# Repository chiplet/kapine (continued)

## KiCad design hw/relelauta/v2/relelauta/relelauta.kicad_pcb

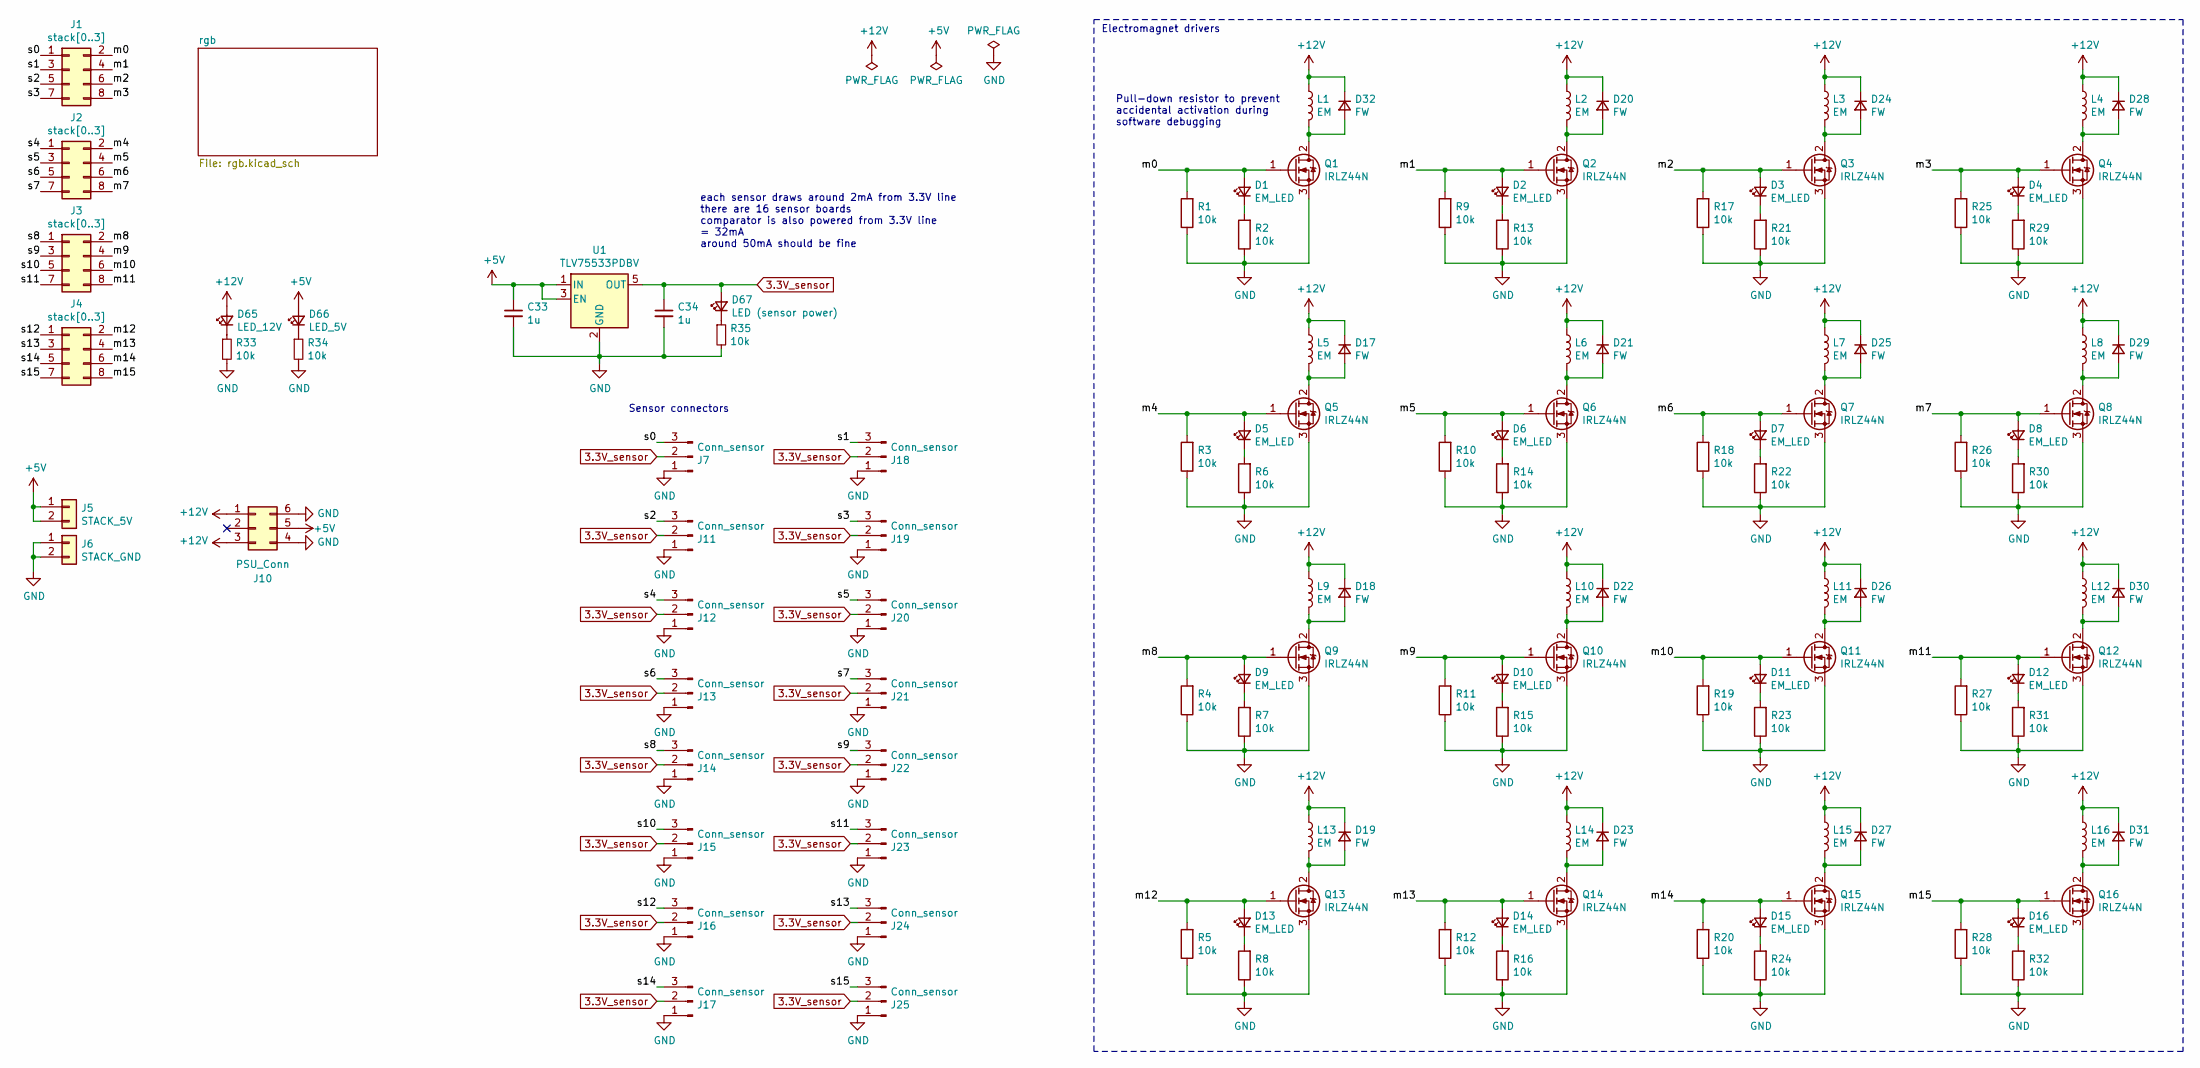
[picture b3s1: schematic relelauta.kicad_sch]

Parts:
C33, C34: 1u; C_0603_1608Metric
D1, D2, D3, D4, D5, D6, D7, D8, D9, D10, D11, D12, D13, D14, D15, D16: EM_LED; LED_0805_2012Metric
D17, D18, D19, D20, D21, D22, D23, D24, D25, D26, D27, D28, D29, D30, D31, D32: FW; D_DO-41_SOD81_P7.62mm_Horizontal
D65: LED_12V; LED_0805_2012Metric
D66: LED_5V; LED_0805_2012Metric
D67: LED (sensor power); LED_0805_2012Metric
J1, J2, J3, J4: stack[0..3]; PinSocket_2x04_P2.54mm_Vertical
J5: STACK_5V; PinSocket_1x02_P2.54mm_Vertical
J6: STACK_GND; PinSocket_1x02_P2.54mm_Vertical
J7, J11, J12, J13, J14, J15, J16, J17, J18, J19, J20, J21, J22, J23, J24, J25: Conn_sensor; PinHeader_1x03_P2.54mm_Horizontal
J10: PSU_Conn; Molex_Mini-Fit_Jr_5566-06A_2x03_P4.20mm_Vertical
L1, L2, L3, L4, L5, L6, L7, L8, L9, L10, L11, L12, L13, L14, L15, L16: EM; TerminalBlock_bornier-2_P5.08mm
Q1, Q2, Q3, Q4, Q5, Q6, Q7, Q8, Q9, Q10, Q11, Q12, Q13, Q14, Q15, Q16: IRLZ44N; TO-220-3_Vertical
R1, R2, R3, R4, R5, R6, R7, R8, R9, R10, R11, R12, R13, R14, R15, R16, R17, R18, R19, R20, R21, R22, R23, R24, R25, R26, R27, R28, R29, R30, R31, R32: 10k; R_0603_1608Metric
R33, R34, R35: 10k; R_0805_2012Metric
U1: TLV75533PDBV; SOT-23-5

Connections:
3.3V_sensor: C34.1, D67.2 (A), J7.2, J11.2, J12.2, J13.2, J14.2, J15.2, J16.2, J17.2, J18.2, J19.2, J20.2, J21.2, J22.2, J23.2, J24.2, J25.2, U1.5 (OUT)
+5V: C33.1, D66.2 (A), J5.1, J5.2, J10.5, U1.1 (IN), U1.3 (EN)
+12V: D17.1 (K), D18.1 (K), D19.1 (K), D20.1 (K), D21.1 (K), D22.1 (K), D23.1 (K), D24.1 (K), D25.1 (K), D26.1 (K), D27.1 (K), D28.1 (K), D29.1 (K), D30.1 (K), D31.1 (K), D32.1 (K), D65.2 (A), J10.1, J10.3, L1.1, L2.1, L3.1, L4.1, L5.1, L6.1, L7.1, L8.1, L9.1, L10.1, L11.1, L12.1, L13.1, L14.1, L15.1, L16.1
/m0: D1.2 (A), J1.2, Q1.1 (G), R1.2
/m1: D2.2 (A), J1.4, Q2.1 (G), R9.2
/m2: D3.2 (A), J1.6, Q3.1 (G), R17.2
/m3: D4.2 (A), J1.8, Q4.1 (G), R25.2
/m4: D5.2 (A), J2.2, Q5.1 (G), R3.2
/m5: D6.2 (A), J2.4, Q6.1 (G), R10.2
/m6: D7.2 (A), J2.6, Q7.1 (G), R18.2
/m7: D8.2 (A), J2.8, Q8.1 (G), R26.2
/m8: D9.2 (A), J3.2, Q9.1 (G), R4.2
/m9: D10.2 (A), J3.4, Q10.1 (G), R11.2
/m10: D11.2 (A), J3.6, Q11.1 (G), R19.2
/m11: D12.2 (A), J3.8, Q12.1 (G), R27.2
/m12: D13.2 (A), J4.2, Q13.1 (G), R5.2
/m13: D14.2 (A), J4.4, Q14.1 (G), R12.2
/m14: D15.2 (A), J4.6, Q15.1 (G), R20.2
/m15: D16.2 (A), J4.8, Q16.1 (G), R28.2
/s0: J1.1, J7.3
/s1: J1.3, J18.3
/s2: J1.5, J11.3
/s3: J1.7, J19.3
/s4: J2.1, J12.3
/s5: J2.3, J20.3
/s6: J2.5, J13.3
/s7: J2.7, J21.3
/s8: J3.1, J14.3
/s9: J3.3, J22.3
/s10: J3.5, J15.3
/s11: J3.7, J23.3
/s12: J4.1, J16.3
/s13: J4.3, J24.3
/s14: J4.5, J17.3
/s15: J4.7, J25.3
GND: C33.2, C34.2, J6.1, J6.2, J7.1, J10.4, J10.6, J11.1, J12.1, J13.1, J14.1, J15.1, J16.1, J17.1, J18.1, J19.1, J20.1, J21.1, J22.1, J23.1, J24.1, J25.1, Q1.3 (S), Q2.3 (S), Q3.3 (S), Q4.3 (S), Q5.3 (S), Q6.3 (S), Q7.3 (S), Q8.3 (S), Q9.3 (S), Q10.3 (S), Q11.3 (S), Q12.3 (S), Q13.3 (S), Q14.3 (S), Q15.3 (S), Q16.3 (S), R1.1, R2.1, R3.1, R4.1, R5.1, R6.1, R7.1, R8.1, R9.1, R10.1, R11.1, R12.1, R13.1, R14.1, R15.1, R16.1, R17.1, R18.1, R19.1, R20.1, R21.1, R22.1, R23.1, R24.1, R25.1, R26.1, R27.1, R28.1, R29.1, R30.1, R31.1, R32.1, R33.2, R34.2, R35.2, U1.2 (GND); also elsewhere on the board
unnamed: D1.1 (K), R2.2
unnamed: D2.1 (K), R13.2
unnamed: D3.1 (K), R21.2
unnamed: D4.1 (K), R29.2
unnamed: D5.1 (K), R6.2
unnamed: D6.1 (K), R14.2
unnamed: D7.1 (K), R22.2
unnamed: D8.1 (K), R30.2
unnamed: D9.1 (K), R7.2
unnamed: D10.1 (K), R15.2
unnamed: D11.1 (K), R23.2
unnamed: D12.1 (K), R31.2
unnamed: D13.1 (K), R8.2
unnamed: D14.1 (K), R16.2
unnamed: D15.1 (K), R24.2
unnamed: D16.1 (K), R32.2
unnamed: D17.2 (A), L5.2, Q5.2 (D)
unnamed: D18.2 (A), L9.2, Q9.2 (D)
unnamed: D19.2 (A), L13.2, Q13.2 (D)
unnamed: D20.2 (A), L2.2, Q2.2 (D)
unnamed: D21.2 (A), L6.2, Q6.2 (D)
unnamed: D22.2 (A), L10.2, Q10.2 (D)
unnamed: D23.2 (A), L14.2, Q14.2 (D)
unnamed: D24.2 (A), L3.2, Q3.2 (D)
unnamed: D25.2 (A), L7.2, Q7.2 (D)
unnamed: D26.2 (A), L11.2, Q11.2 (D)
unnamed: D27.2 (A), L15.2, Q15.2 (D)
unnamed: D28.2 (A), L4.2, Q4.2 (D)
unnamed: D29.2 (A), L8.2, Q8.2 (D)
unnamed: D30.2 (A), L12.2, Q12.2 (D)
unnamed: D31.2 (A), L16.2, Q16.2 (D)
unnamed: D32.2 (A), L1.2, Q1.2 (D)
unnamed: D65.1 (K), R33.1
unnamed: D66.1 (K), R34.1
unnamed: D67.1 (K), R35.1

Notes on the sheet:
Pull-down resistor to prevent accidental activation during software debugging
each sensor draws around 2mA from 3.3V line there are 16 sensor boards comparator is also powered from 3.3V line = 32mA around 50mA should be fine
Sensor connectors
Electromagnet drivers

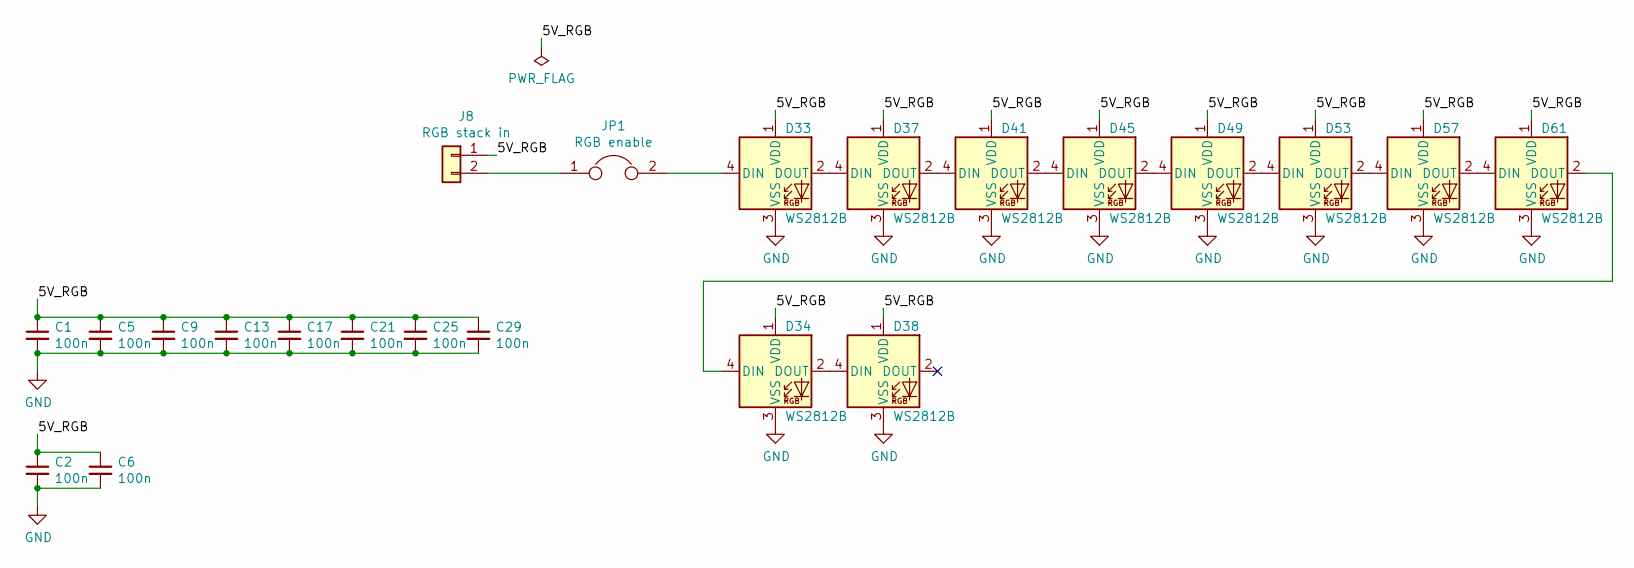
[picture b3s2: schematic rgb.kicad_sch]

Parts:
C1, C2, C5, C6, C9, C13, C17, C21, C25, C29: 100n; C_0603_1608Metric
D33, D34, D37, D38, D41, D45, D49, D53, D57, D61: WS2812B; LED_WS2812B_PLCC4_5.0x5.0mm_P3.2mm
J8: RGB stack in; PinSocket_1x02_P2.54mm_Vertical
JP1: RGB enable; PinHeader_2x01_P2.54mm_Vertical

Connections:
/rgb/5V_RGB: C1.1, C2.1, C5.1, C6.1, C9.1, C13.1, C17.1, C21.1, C25.1, C29.1, D33.1 (VDD), D34.1 (VDD), D37.1 (VDD), D38.1 (VDD), D41.1 (VDD), D45.1 (VDD), D49.1 (VDD), D53.1 (VDD), D57.1 (VDD), D61.1 (VDD), J8.1
GND: C1.2, C2.2, C5.2, C6.2, C9.2, C13.2, C17.2, C21.2, C25.2, C29.2, D33.3 (VSS), D34.3 (VSS), D37.3 (VSS), D38.3 (VSS), D41.3 (VSS), D45.3 (VSS), D49.3 (VSS), D53.3 (VSS), D57.3 (VSS), D61.3 (VSS); also elsewhere on the board
unnamed: D33.2 (DOUT), D37.4 (DIN)
unnamed: D33.4 (DIN), JP1.2
unnamed: D34.2 (DOUT), D38.4 (DIN)
unnamed: D34.4 (DIN), D61.2 (DOUT)
unnamed: D37.2 (DOUT), D41.4 (DIN)
unnamed: D41.2 (DOUT), D45.4 (DIN)
unnamed: D45.2 (DOUT), D49.4 (DIN)
unnamed: D49.2 (DOUT), D53.4 (DIN)
unnamed: D53.2 (DOUT), D57.4 (DIN)
unnamed: D57.2 (DOUT), D61.4 (DIN)
unnamed: J8.2, JP1.1

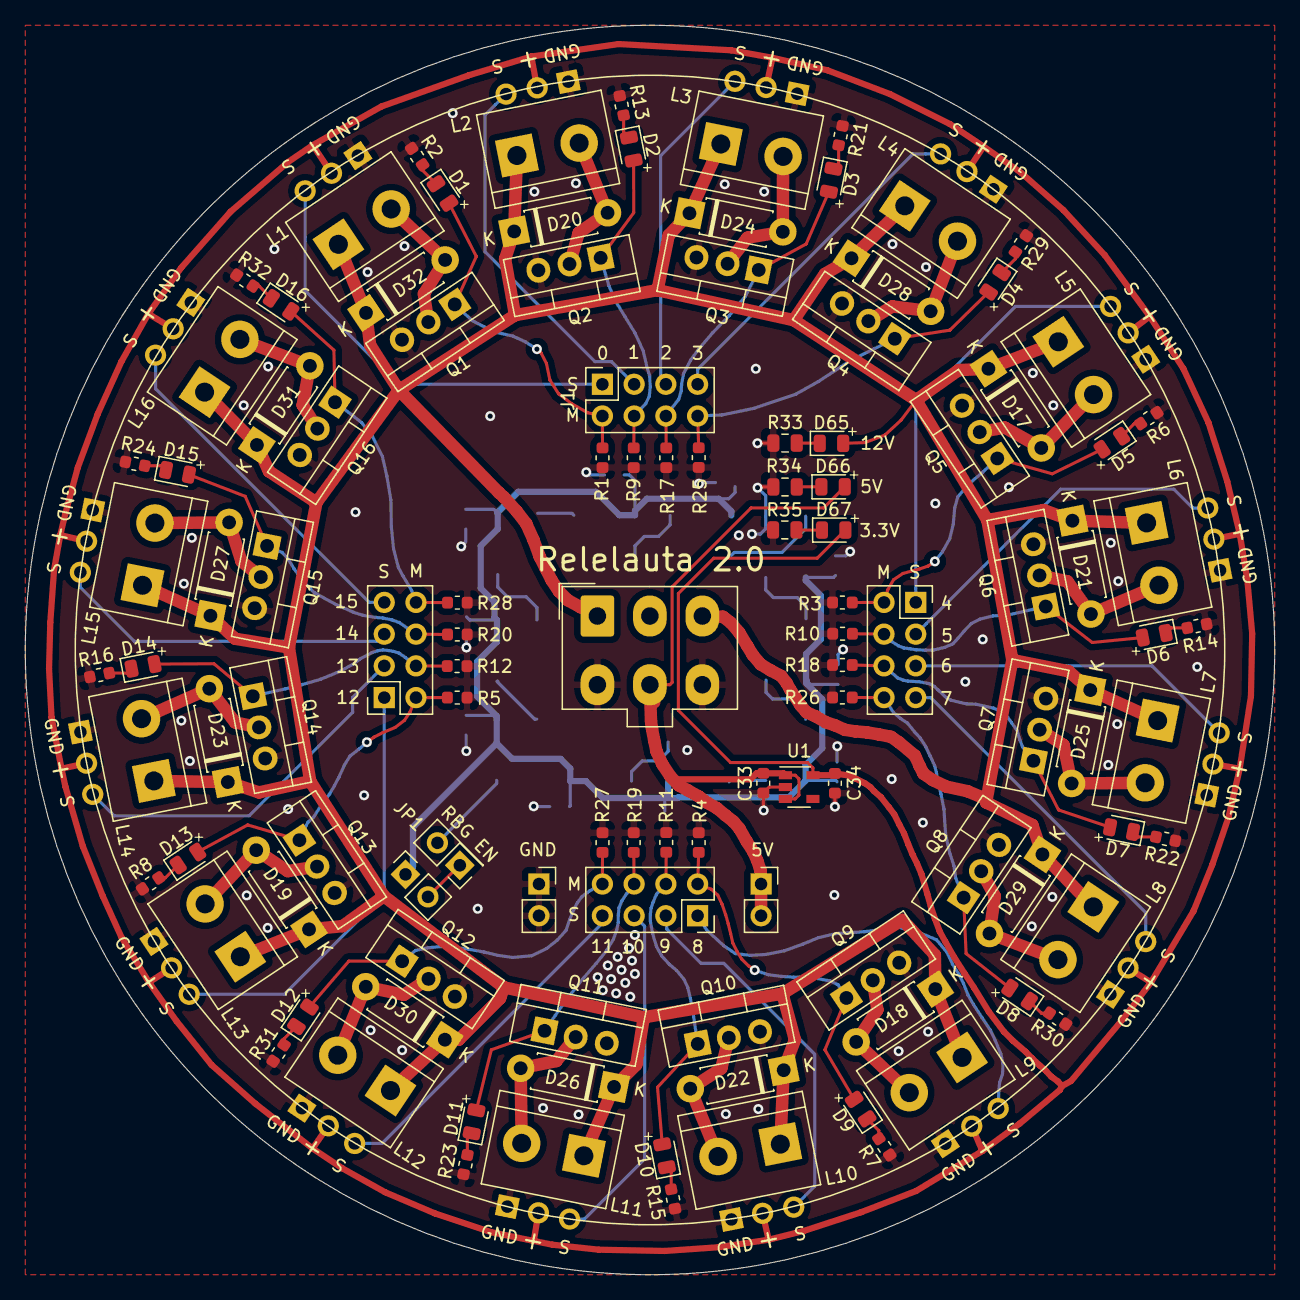
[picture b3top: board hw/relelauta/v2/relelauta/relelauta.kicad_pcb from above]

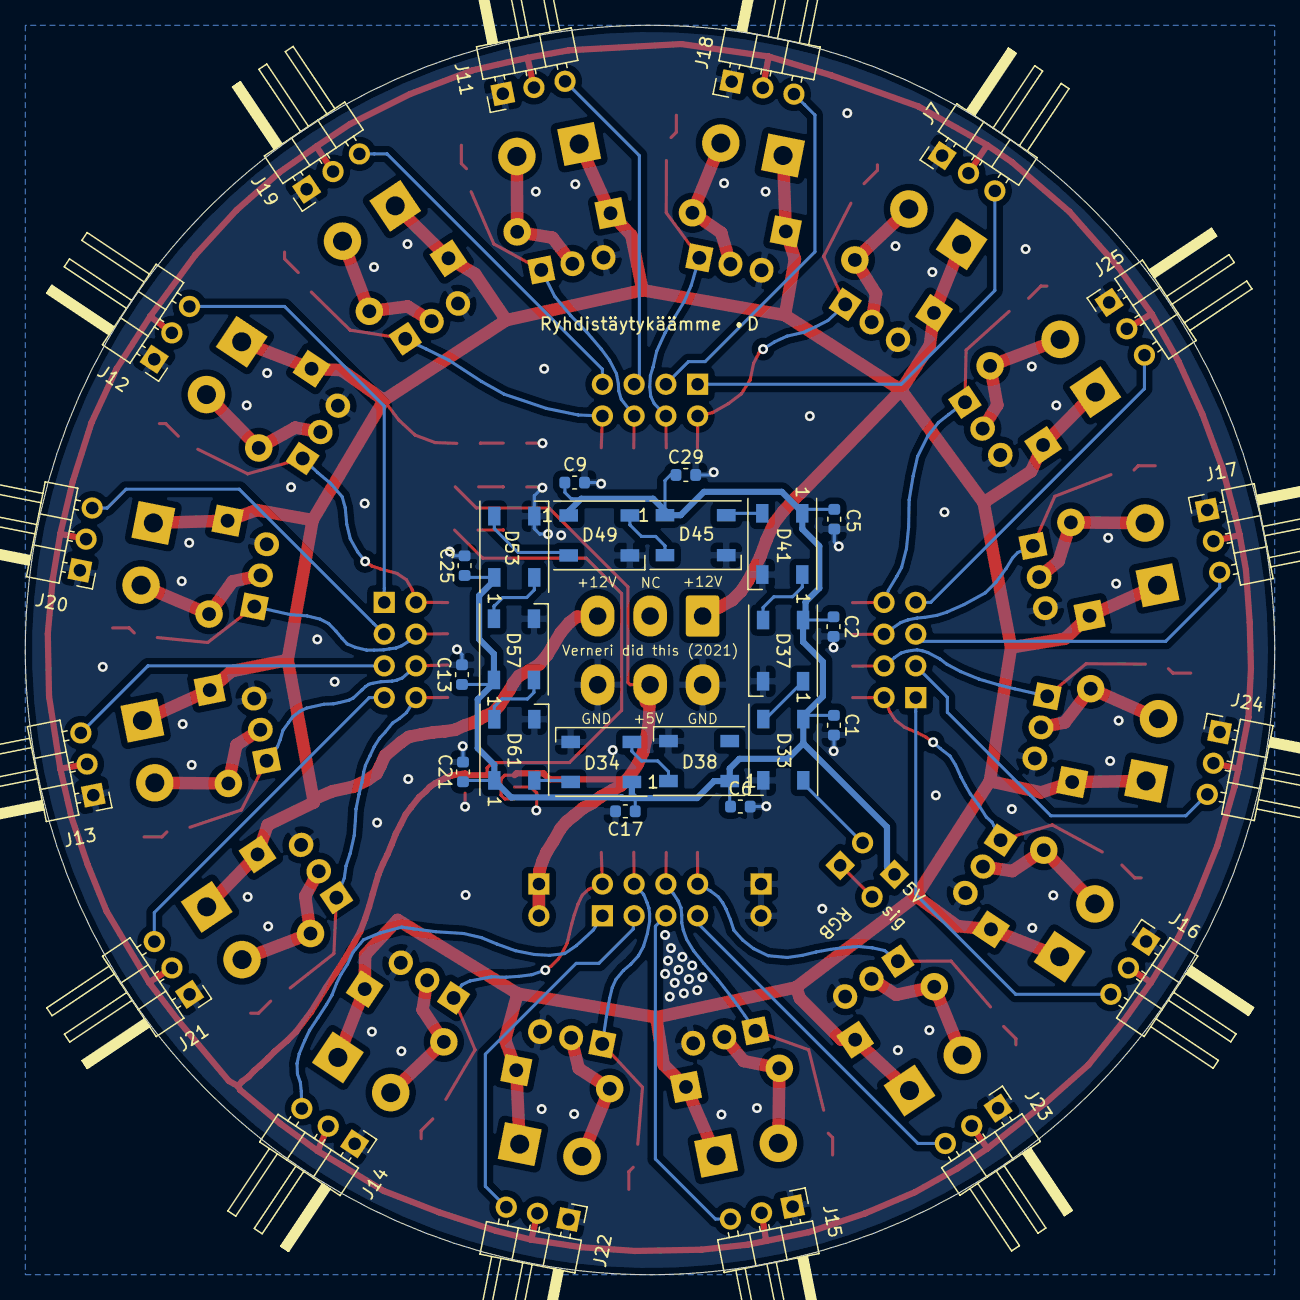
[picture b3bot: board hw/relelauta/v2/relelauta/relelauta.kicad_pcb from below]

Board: 2 copper layers, 100.0 x 100.0 mm, 150 parts (36 on the bottom side), 83 nets.

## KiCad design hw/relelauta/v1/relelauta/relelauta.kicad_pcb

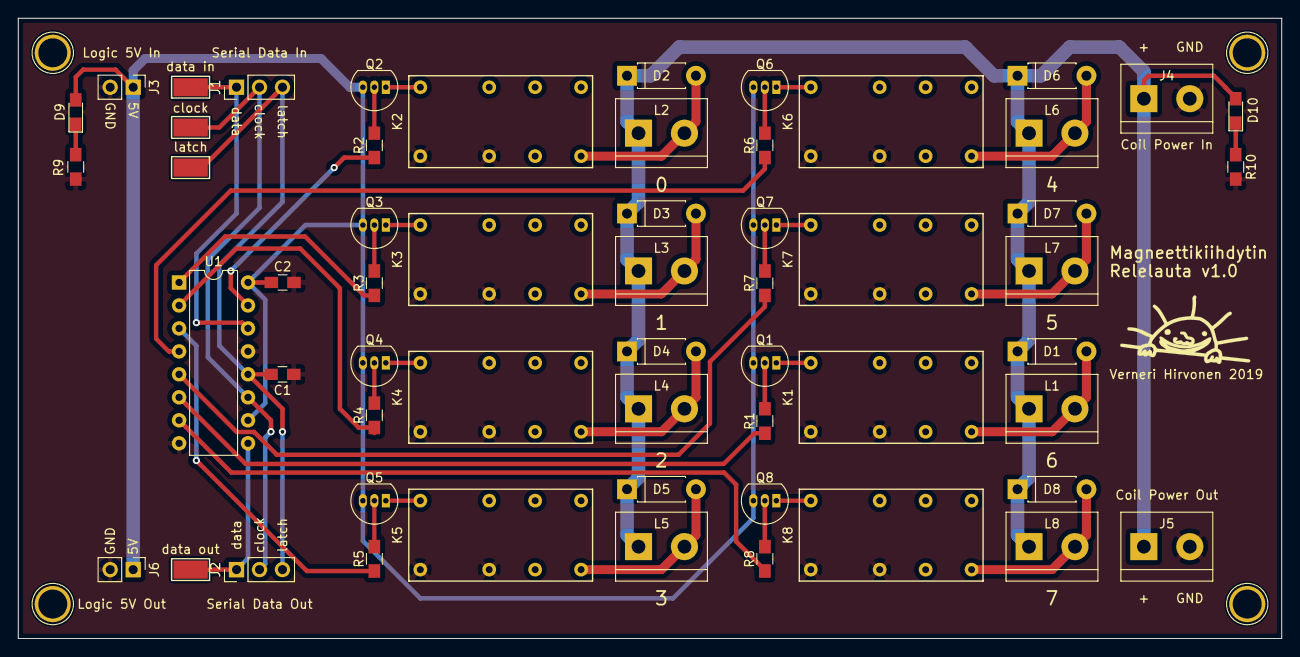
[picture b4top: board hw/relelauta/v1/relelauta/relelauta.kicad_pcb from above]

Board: 2 copper layers, 139.7 x 68.6 mm, 57 parts (0 on the bottom side), 41 nets.

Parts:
C1, C2: 100n; C_0805_HandSoldering
D1, D2, D3, D4, D5, D6, D7, D8: 1N4001; D_DO-41_SOD81_P7.62mm_Horizontal
D9: ARDUINO; LED_0805_HandSoldering
D10: COIL; LED_0805_HandSoldering
J1: serial_in; Pin_Header_Straight_1x03_Pitch2.54mm
J2: serial_out; Pin_Header_Straight_1x03_Pitch2.54mm
J3: arduino_5V; Pin_Header_Straight_1x02_Pitch2.54mm
J4: coil_power_in; TerminalBlock_bornier-2_P5.08mm
J5: coil_power_out; TerminalBlock_bornier-2_P5.08mm
J6: 5V_out; Pin_Header_Straight_1x02_Pitch2.54mm
K1: relay 7; RY5W-K
K2: relay 1; RY5W-K
K3: relay 2; RY5W-K
K4: relay 3; RY5W-K
K5: relay 4; RY5W-K
K6: relay 5; RY5W-K
K7: relay 6; RY5W-K
K8: relay 8; RY5W-K
L1: coil7; TerminalBlock_bornier-2_P5.08mm
L2: coil1; TerminalBlock_bornier-2_P5.08mm
L3: coil2; TerminalBlock_bornier-2_P5.08mm
L4: coil3; TerminalBlock_bornier-2_P5.08mm
L5: coil4; TerminalBlock_bornier-2_P5.08mm
L6: coil5; TerminalBlock_bornier-2_P5.08mm
L7: coil6; TerminalBlock_bornier-2_P5.08mm
L8: coil8; TerminalBlock_bornier-2_P5.08mm
Q1, Q2, Q3, Q4, Q5, Q6, Q7, Q8: 2N3904; TO-92_Inline_Narrow_Oval
R1, R2, R3, R4, R5, R6, R7, R8: 1k; R_0805_HandSoldering
R9, R10: 10k; R_0805_HandSoldering
U1: 74HC595; DIP-16_W7.62mm
clock: clock; Test_Point_Keystone_5019_Minature
data in: data_in; Test_Point_Keystone_5019_Minature
data out: data_out; Test_Point_Keystone_5019_Minature
latch: latch; Test_Point_Keystone_5019_Minature

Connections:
+5V: C2.1, D9.2, J3.1, J6.1, Q1.3, Q2.3, Q3.3, Q4.3, Q5.3, Q6.3, Q7.3, Q8.3, U1.10, U1.16
GND: C1.1, C2.2, J3.2, J4.2, J5.2, J6.2, K1.21, K1.A2, K2.21, K2.A2, K3.21, K3.A2, K4.21, K4.A2, K5.21, K5.A2, K6.21, K6.A2, K7.21, K7.A2, K8.21, K8.A2, R9.2, R10.2, U1.8, U1.13
unnamed: D1.2, K1.24, L1.2
unnamed: D2.2, K2.24, L2.2
unnamed: D3.2, K3.24, L3.2
unnamed: D4.2, K4.24, L4.2
unnamed: D5.2, K5.24, L5.2
unnamed: D6.2, K6.24, L6.2
unnamed: D7.2, K7.24, L7.2
unnamed: D8.2, K8.24, L8.2
unnamed: D9.1, R9.1
unnamed: D10.1, R10.1
unnamed: K1.A1, Q1.1
unnamed: K2.A1, Q2.1
unnamed: K3.A1, Q3.1
unnamed: K4.A1, Q4.1
unnamed: K5.A1, Q5.1
unnamed: K6.A1, Q6.1
unnamed: K7.A1, Q7.1
unnamed: K8.A1, Q8.1
unnamed: Q1.2, R1.2
unnamed: Q2.2, R2.2
unnamed: Q3.2, R3.2
unnamed: Q4.2, R4.2
unnamed: Q5.2, R5.2
unnamed: Q6.2, R6.2
unnamed: Q7.2, R7.2
unnamed: Q8.2, R8.2
V_coil: D1.1, D2.1, D3.1, D4.1, D5.1, D6.1, D7.1, D8.1, D10.2, J4.1, J5.1, L1.1, L2.1, L3.1, L4.1, L5.1, L6.1, L7.1, L8.1
clock: J1.2, J2.2, U1.11, clock.1
data_in: J1.1, U1.14, data in.1
data_out: J2.1, U1.9, data out.1
latch: C1.2, J1.3, J2.3, U1.12, latch.1
signal1: R2.1, U1.15
signal2: R3.1, U1.1
signal3: R4.1, U1.2
signal4: R5.1, U1.3
signal5: R6.1, U1.4
signal6: R7.1, U1.5
signal7: R1.1, U1.6
signal8: R8.1, U1.7

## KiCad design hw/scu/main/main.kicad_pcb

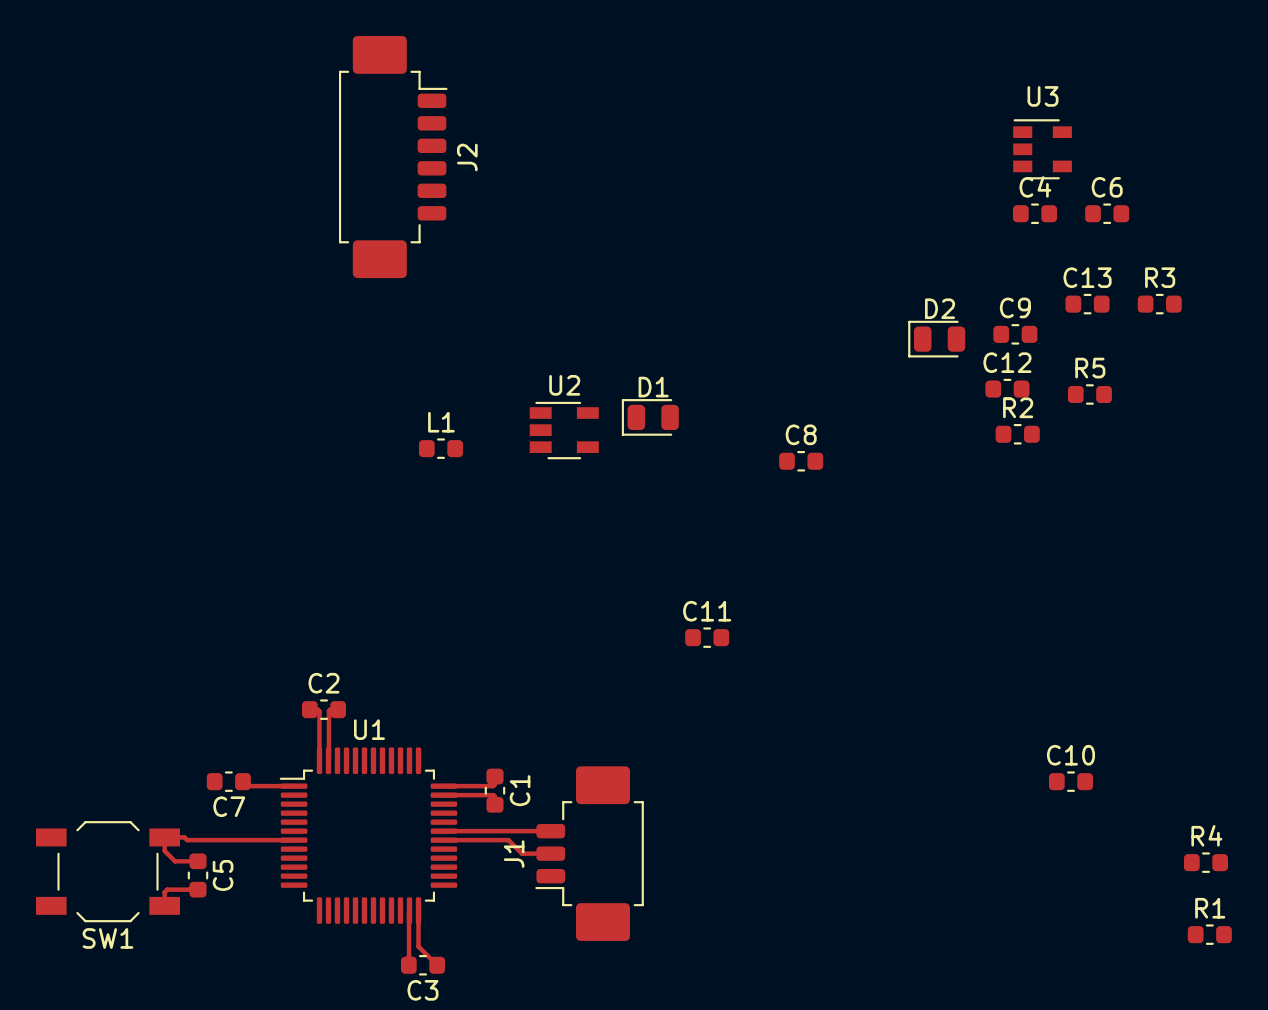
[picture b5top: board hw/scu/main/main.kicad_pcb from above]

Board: 2 copper layers, 27 parts (0 on the bottom side), 16 nets.

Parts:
C1, C2, C3, C5, C7: 100n; C_0603_1608Metric
C4, C9, C11: 4.7u; C_0603_1608Metric
C6: 10n; C_0603_1608Metric
C8, C10, C12: 1u; C_0603_1608Metric
C13: 10u; C_0603_1608Metric
D1, D2: LED; LED_0805_2012Metric
J1: Conn_01x03_MountingPin; Molex_PicoBlade_53261-0371_1x03-1MP_P1.25mm_Horizontal
J2: Conn_01x06_MountingPin; Molex_PicoBlade_53261-0671_1x06-1MP_P1.25mm_Horizontal
L1: 10u; L_0603_1608Metric
R1, R2, R3, R4: 10k; R_0603_1608Metric
R5: 470k; R_0603_1608Metric
SW1: SW_Push; SW_SPST_TL3342
U1: STM32F072C8Tx; LQFP-48_7x7mm_P0.5mm
U2: LM3670MF; TSOT-23-5
U3: LP5907MFX-3.3; SOT-23-5

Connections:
/3V3_A: C6.1, C8.1, C12.1, U1.9, U3.5
/3V3_D: C1.1, C2.1, C3.1, C4.1, C7.1, C9.1, C13.1, J2.1, L1.2, R4.2, U1.1, U1.24, U1.36, U1.48, U2.4
/LED_1: D1.2, U1.27
/LED_2: D2.2, U1.28
/NRST: C5.1, J2.5, SW1.2, U1.7
/SWCLK: J2.2, U1.37
/SWDIO: J2.4, U1.34
/USART1_RX: J1.3, U1.31
/USART1_TX: J1.2, U1.30
/V_USB: C10.1, C11.1, R5.1, U2.1, U2.3, U3.1
GND: C1.2, C2.2, C3.2, C4.2, C5.2, C6.2, C7.2, C8.2, C9.2, C10.2, C11.2, C12.2, C13.2, J1.1, J1.MP, J2.3, J2.MP, R1.2, R2.1, R3.1, SW1.1, U1.8, U1.23, U1.35, U1.47, U2.2, U3.2
unnamed: D1.1, R2.2
unnamed: D2.1, R3.2
unnamed: L1.1, U2.5
unnamed: R1.1, R4.1, U1.44
unnamed: R5.2, U3.3

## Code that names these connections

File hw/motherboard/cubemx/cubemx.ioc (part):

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Mcu.UserName=STM32F303RETx
PC10.Signal=GPIO_Input
PC12.Signal=GPIO_Input
PB11.Signal=GPIO_Output
PB13.Signal=GPIO_Input
PB15.Signal=GPIO_Input
PA12.Signal=GPIO_Output
PB6.Signal=GPIO_Input
PC7.Signal=GPIO_Input
PC3.Signal=GPIO_Output
RCC.HSE_VALUE=8000000
PB2.Signal=GPIO_Output
PB7.Signal=GPIO_Output
PA8.Signal=GPIO_Output
PA0.Signal=GPIO_Output
Mcu.Package=LQFP64
PB9.Signal=GPIO_Output
PB1.Signal=GPIO_Input
PA10.Signal=USART1_RX
PA15.Signal=SYS_JTDI
PC5.Signal=GPIO_Output
PB4.Signal=GPIO_Input
PA3.Signal=GPIO_Output
PA10.Mode=Asynchronous
PC11.Signal=GPIO_Output
PC13.Signal=GPIO_Output
PC8.Signal=GPIO_Output
PC4.Signal=GPIO_Input
PC2.Signal=GPIO_Input
PC6.Signal=GPIO_Output
PC0.Signal=GPIO_Input
PA13.Signal=SYS_JTMS-SWDIO
PA9.Mode=Asynchronous
PA9.Signal=USART1_TX
PA1.Signal=GPIO_Output
PB10.Signal=GPIO_Input
PB14.Signal=GPIO_Output
board=custom
Mcu.Name=STM32F303R(D-E)Tx
PA2.Signal=GPIO_Input
PB3.Signal=SYS_JTDO-TRACESWO
RCC.SYSCLKFreq_VALUE=8000000
PB5.Signal=GPIO_Output
PA11.Signal=GPIO_Input
PA14.Signal=SYS_JTCK-SWCLK
PB8.Signal=GPIO_Input
PC9.Signal=GPIO_Input
PD2.Signal=GPIO_Output
PC1.Signal=GPIO_Output

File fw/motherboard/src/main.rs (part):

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        // dispatchers = [USB_HP, USB_LP, USB_WKUP_EXTI, TIM20_BRK, TIM20_UP, TIM20_TRG_COM, TIM20_CC, SPI4, I2C3_ER, I2C3_EV]
)]
mod app {
    use stm32f3xx_hal::{gpio::{self, gpioa::{self, Parts}, marker::Gpio, Pin, AF5, PA5, PA6, PA7, U}, pac::{DMA1, GPIOA, SPI1}, rcc::{Enable, Reset}, spi::Spi};

    use super::*;
    const SENSOR_LUT: [usize; 16] = [13, 9, 11, 2, 0, 12, 15, 5, 14, 4, 8, 3, 1, 7, 10, 6];
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        debug_leds: [PXx<Output<PushPull>>; 2],
        local_cnt: u8,
        spi1: SPI1,
        // spi: Spi<SPI1, (PA5<AF5<PushPull>>, PA6<AF5<PushPull>>, PA7<AF5<PushPull>>)>
    }

    #[init]
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
        // let uart_pins = (
        //     gpio_a
        //         .pa9
        //         .into_af_push_pull(&mut gpio_a.moder, &mut gpio_a.otyper, &mut gpio_a.afrh),
        //     gpio_a
        //         .pa10
        //         .into_af_push_pull(&mut gpio_a.moder, &mut gpio_a.otyper, &mut gpio_a.afrh),
        // );

        // use SPI1 peripheral to drive WS2812B RGB leds
        let spi1_mosi = gpio_a
            .pa7
            .into_af_push_pull::<5>(&mut gpio_a.moder, &mut gpio_a.otyper, &mut gpio_a.afrl);

        // Manual SPI1 configuration
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        // debug LEDs
        let mut debug_leds: [PXx<Output<PushPull>>; 2] = [
            gpio_a
                .pa0
                .into_push_pull_output(&mut gpio_a.moder, &mut gpio_a.otyper)
                .downgrade()
                .downgrade(),
            gpio_a
                .pa1
                .into_push_pull_output(&mut gpio_a.moder, &mut gpio_a.otyper)
                .downgrade()
                .downgrade(),
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        // electromagnet outputs
        let mut magnets: [PXx<Output<PushPull>>; 16] = [
            gpio_b
                .pb5
                .into_push_pull_output(&mut gpio_b.moder, &mut gpio_b.otyper)
                .downgrade()
                .downgrade(),
            gpio_d
                .pd2
                .into_push_pull_output(&mut gpio_d.moder, &mut gpio_d.otyper)
                .downgrade()
                .downgrade(),
            gpio_c
                .pc11
                .into_push_pull_output(&mut gpio_c.moder, &mut gpio_c.otyper)
                .downgrade()
                .downgrade(),
            gpio_a
                .pa12
                .into_push_pull_output(&mut gpio_a.moder, &mut gpio_a.otyper)
                .downgrade()
                .downgrade(),
            gpio_a
                .pa8
                .into_push_pull_output(&mut gpio_a.moder, &mut gpio_a.otyper)
                .downgrade()
                .downgrade(),
            gpio_c
                .pc8
                .into_push_pull_output(&mut gpio_c.moder, &mut gpio_c.otyper)
                .downgrade()
                .downgrade(),
            gpio_c
                .pc6
                .into_push_pull_output(&mut gpio_c.moder, &mut gpio_c.otyper)
                .downgrade()
                .downgrade(),
            gpio_b
                .pb14
                .into_push_pull_output(&mut gpio_b.moder, &mut gpio_b.otyper)
                .downgrade()
                .downgrade(),
            gpio_b
                .pb11
                .into_push_pull_output(&mut gpio_b.moder, &mut gpio_b.otyper)
                .downgrade()
                .downgrade(),
            gpio_b
                .pb2
                .into_push_pull_output(&mut gpio_b.moder, &mut gpio_b.otyper)
                .downgrade()
                .downgrade(),
            gpio_c
                .pc5
                .into_push_pull_output(&mut gpio_c.moder, &mut gpio_c.otyper)
                .downgrade()
                .downgrade(),
            gpio_a
                .pa4
                .into_push_pull_output(&mut gpio_a.moder, &mut gpio_a.otyper)
                .downgrade()
                .downgrade(), // m11 (bodge)
            gpio_c
                .pc3
                .into_push_pull_output(&mut gpio_c.moder, &mut gpio_c.otyper)
                .downgrade()
                .downgrade(),
            gpio_c
                .pc1
                .into_push_pull_output(&mut gpio_c.moder, &mut gpio_c.otyper)
                .downgrade()
                .downgrade(),
            gpio_b
                .pb9
                .into_push_pull_output(&mut gpio_b.moder, &mut gpio_b.otyper)
                .downgrade()
                .downgrade(),
            gpio_b
                .pb7
                .into_push_pull_output(&mut gpio_b.moder, &mut gpio_b.otyper)
                .downgrade()
                .downgrade(),
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
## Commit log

2019-03-02 Added source code
2019-03-17 Moved kiihdytin sketch to a directory
2019-05-28 Completed board schematic
2019-05-28 Add test points and useful connectors
2019-05-29 Completed PCB layout
2019-05-29 Fixed NPN transistors on the wrong side of load in the schematic by changing them to PNP transistors.
2019-05-31 Added a hello world version of the Control Panel
2019-06-06 Add pom.xml for Maven
2019-07-06 Working prototype 1 acceleration sequence
2019-07-13 Fix javafx problems related to developing on mac
2019-07-13 Add serial latency test for java-arduino communication
2019-07-14 Ditch FXML and fix serial communication with Arduino
2019-07-18 Add initial control panel UI
2019-07-19 Switch NB to IntelliJ and add some unfinished serial comm classes
2019-07-19 Improve scaling when window is resized and add basic chart
2019-08-25 Switch to Gradle
2019-11-04 Remove unused code
2019-12-23 Some old work on the GUI
2020-02-07 Add reference design for STM32F373
2020-02-07 Add RGB leds to schematic
2020-08-17 WIP save progress before including digikey kicad library
2020-08-17 Add digikey-kicad-library schematic symbols to motherboard project
2020-08-17 Add documentation for setting up git submodules for hw development
2020-08-17 Add digikey-kicad-library footprints to motherboard project
2020-08-24 Add cubemx project for pin configuration.
2020-08-24 WIP Start motherboard PCB layout.
2020-09-01 WIP Add electromagnet and sensor schematic connections to MCU pins
2020-09-01 Lay out motherboard hardware revision 1
2020-09-02 Minor motherboard layout changes. Bump revision number to 1.1.
2020-09-02 WIP Add motherboard rev 1.1 pinout documentation
2020-09-03 Add missing component values.
2020-09-03 Add reverse polarity protection to +5V input. Bump revision number to 1.2.
2021-01-17 Reorganize project directory
2021-01-18 Add stm32f1xx-hal blinky firmware
2021-01-18 New magnet driver demo firmware
2021-02-03 Configure firmware for STM32F303RE MCU
2021-02-09 Update stlink inverface version in openocd config
2021-05-14 Motherboard Revision 1.2. blinky firmware
2021-05-16 WIP USB-Serial
2021-05-16 Working serial example on motherboard hardware
2021-05-17 Add basic message sending functionality
2021-05-18 Blink electromagnet signals
2021-05-19 WIP start adding support for RGB lights
2021-06-02 Add RGB LED microcontroller pin to pinout
2021-07-10 WIP ws2812 demo that compiles but doesn't yet work
2021-08-02 Add module for packet
2021-08-02 Add WIP write_bytes method
2021-08-02 Add write_bytes function
2021-08-02 Add crc16 crate
2021-08-02 Add checksum computation and unit tests
2021-08-02 Reformat to avoid multiple statement in a single line
2021-08-02 Extract packet module to a dedicated crate
2021-08-03 WIP UART receiver with RTIC and interrupts
2021-08-03 Add kapine-packet as a dependency
2021-08-03 Bump kapine-packet version
2021-08-03 Improve code
2021-08-04 Save work before refactor
2021-08-06 WIP save progress before updating stm32f3xx-hal dependency
2021-08-06 WIP start fleshing out sensor interrupts, some hardware bodges are required
2021-08-07 Finish implementing interrupt handlers for sensor inputs
2021-08-07 Send instructions to kapine through the command line
2021-08-07 Add safety timer for magnets
2021-08-07 Update motherboard firmware pinout
2022-08-02 WIP: update dependencies and start fixing resulting issues
2022-08-08 Something's still off with uart rx interrupts
2022-08-08 Somewhat working magnet on commands from PC
2024-07-03 wip: fix motherboard v1.1 bugs
2024-07-03 Check in incomplete SCU hardware
2024-07-03 Remove gitignored files
2024-07-03 Remove dangling gitignore
2024-07-03 Add back digikey-kicad-library
2024-07-03 Create directory for arduino code
2024-07-03 Check in Arduino sketch from old linear prototype
2024-07-03 Add electromagnet driver schematics
2024-07-03 Finish laying out relelauta v2.0 PCB. Minor tweaks to motherboard.
2024-07-03 Add missing silkscreen markings
2024-07-03 Board layouts before checking gerbers for alignment
2024-07-03 Update KiCad files to KiCad 8
2024-07-03 Ignore gerbers
2024-07-03 Remove gerbers
2024-07-03 Update sensorilauta files to KiCad 8
2024-07-03 tweak openocd config
2024-07-04 Working SPI1 transfers, but successive octets are sent too slowly
2024-07-05 Workign sine LUT with one WS2812B led using custom SPI driver
2024-07-05 Laggy pulse animation using DMA transfers for LED values
2024-07-05 Kuul RGB animaatio, mutta yksi ledi lagittaa vielä 😢
2024-07-05 Clean up unused SPI1 PORTA pins
